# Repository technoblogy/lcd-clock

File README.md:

# Low-Power LCD Clock
A low-power LCD clock based on an AVR128DA48.

For more information see http://www.technoblogy.com/show?19K8.

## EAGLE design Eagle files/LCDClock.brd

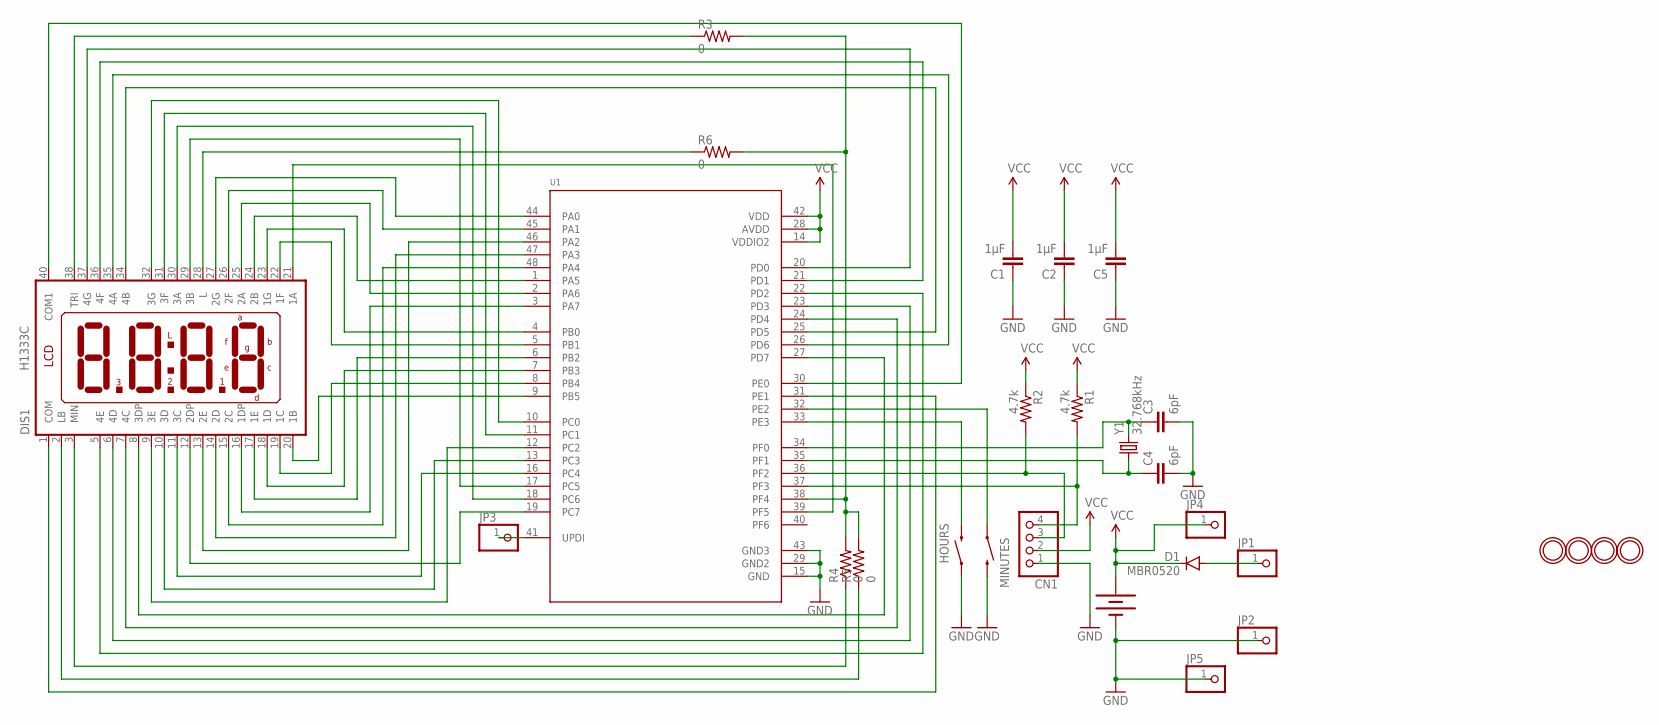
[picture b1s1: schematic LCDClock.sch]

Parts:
BAT1: 20mm coincell; BATTCON_20MM_4LEGS
C1, C2, C5: 1µF; 0805
C3, C4: 6pF; 0805
CN1: JST_4PIN; JSTPH4
D1: MBR0520; SOD-123
DIS1: H1333C
HOURS: SWITCH-MOMENTARY-2SMD-4; TACTILE_SWITCH_TALL
JP1, JP2, JP3: HEADER-1X1ROUND; 1X01_ROUND
JP4, JP5: HEADER-1X12MM; 1X01_2MM
MINUTES: SWITCH-MOMENTARY-2SMD-4; TACTILE_SWITCH_TALL
R1, R2: 4.7k; 0805
R3, R4, R5, R6: 0; 0805
U1: AVR128DB48; LQFP48
U$1, U$4, U$5, U$9: MOUNTINGHOLE2.5; MOUNTINGHOLE_2.5_PLATED
Y1: 32.768kHz; CRYSTAL-SMD-3.2X1.5MM

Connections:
GND: BAT1.NEGATIVE (-), C1.1, C2.1, C3.2, C4.2, C5.1, CN1.1, HOURS.A2 (1), JP2.1, JP5.1, MINUTES.B2 (2), U1.15 (GND), U1.29 (GND2), U1.43 (GND3)
unnamed: DIS1.23 (1G), U1.4 (PB0)
unnamed: DIS1.22 (1F), U1.5 (PB1)
unnamed: DIS1.17 (1E), U1.6 (PB2)
unnamed: DIS1.18 (1D), U1.7 (PB3)
unnamed: DIS1.19 (1C), U1.8 (PB4)
unnamed: DIS1.20 (1B), U1.9 (PB5)
unnamed: DIS1.24 (2B), U1.1 (PA5)
unnamed: DIS1.25 (2A), U1.2 (PA6)
unnamed: DIS1.26 (2F), U1.45 (PA1)
unnamed: MINUTES.A2 (1), U1.32 (PE2)
unnamed: DIS1.27 (2G), U1.44 (PA0)
unnamed: DIS1.16 (1DP), U1.3 (PA7)
unnamed: HOURS.B2 (2), U1.33 (PE3)
unnamed: DIS1.15 (2C), U1.48 (PA4)
unnamed: DIS1.14 (2D), U1.47 (PA3)
unnamed: DIS1.13 (2E), U1.46 (PA2)
unnamed: DIS1.12 (2DP), U1.19 (PC7)
unnamed: DIS1.11 (3C), U1.16 (PC4)
unnamed: DIS1.10 (3D), U1.13 (PC3)
unnamed: DIS1.9 (3E), U1.12 (PC2)
unnamed: DIS1.29 (3B), U1.17 (PC5)
unnamed: DIS1.30 (3A), U1.18 (PC6)
unnamed: DIS1.31 (3F), U1.11 (PC1)
unnamed: DIS1.32 (3G), U1.10 (PC0)
unnamed: DIS1.34 (4B), U1.25 (PD5)
unnamed: DIS1.35 (4A), U1.26 (PD6)
unnamed: CN1.3, R2.2, U1.36 (PF2)
unnamed: DIS1.36 (4F), U1.21 (PD1)
unnamed: CN1.4, R1.2, U1.37 (PF3)
unnamed: DIS1.37 (4G), U1.20 (PD0)
unnamed: DIS1.8 (3DP), U1.27 (PD7)
unnamed: DIS1.7 (4C), U1.24 (PD4)
unnamed: DIS1.6 (4D), U1.23 (PD3)
unnamed: DIS1.5 (4E), U1.22 (PD2)
unnamed: DIS1.21 (1A), U1.39 (PF5)
unnamed: R3.2, R4.2, R5.2, R6.2, U1.38 (PF4)
unnamed: DIS1.40 (COM1), U1.30 (PE0)
unnamed: DIS1.1 (COM), U1.31 (PE1)
unnamed: C4.1, U1.35 (PF1), Y1.P$1 (1)
unnamed: JP3.1, U1.41 (UPDI)
unnamed: C3.1, U1.34 (PF0), Y1.P$2 (2)
unnamed: DIS1.38 (TRI), R3.1
unnamed: DIS1.28 (L), R6.1
unnamed: DIS1.3 (MIN), R4.1
unnamed: DIS1.2 (LB), R5.1
unnamed: D1.A, JP1.1
VCC: BAT1.POSITIVE@1 (+), BAT1.POSITIVE@2 (+), BAT1.POSITIVE@3 (+), BAT1.POSITIVE@4 (+), C1.2, C2.2, C5.2, CN1.2, D1.C, JP4.1, R1.1, R2.1, U1.14 (VDDIO2), U1.28 (AVDD), U1.42 (VDD)

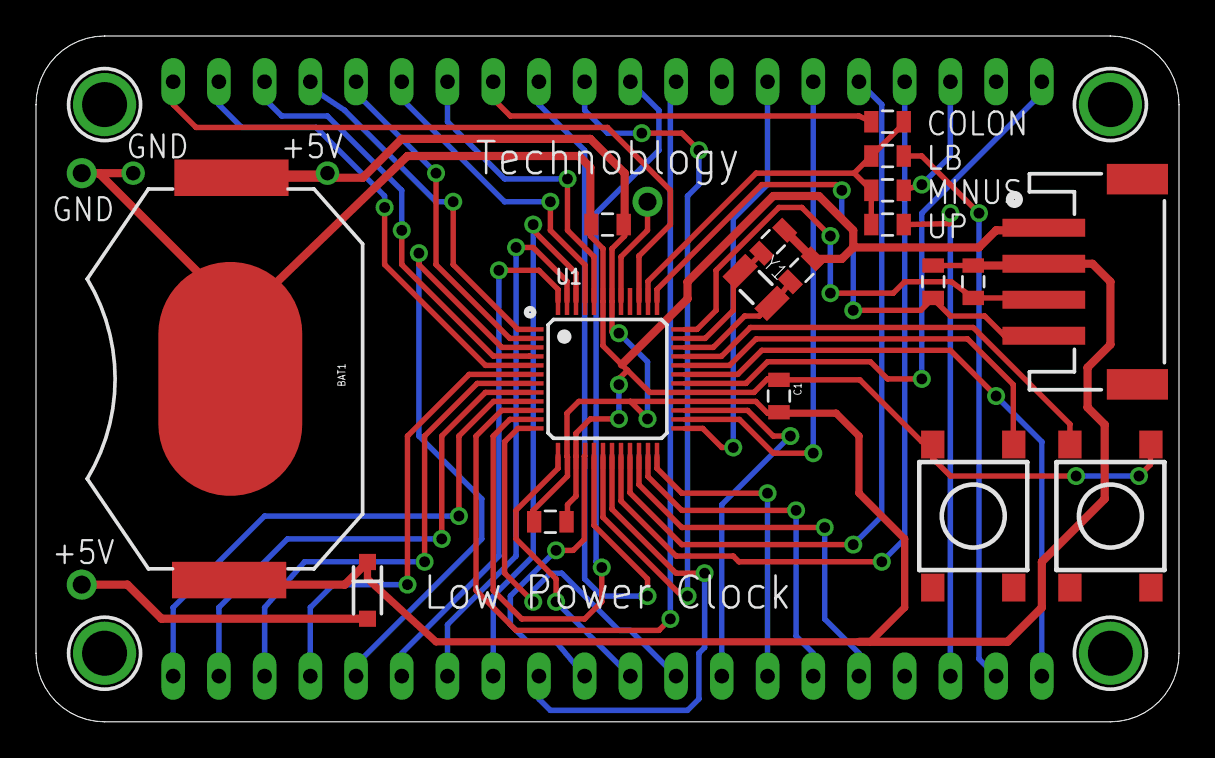
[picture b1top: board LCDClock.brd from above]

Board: 2 copper layers, 63.5 x 38.1 mm, 28 parts (1 on the bottom side), 48 nets.

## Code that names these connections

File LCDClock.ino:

/* Low-Power LCD Clock

   David Johnson-Davies - www.technoblogy.com - 4th May 2021
   AVR128DA48 @ 24 MHz (internal oscillator; BOD disabled)
   
   CC BY 4.0
   Licensed under a Creative Commons Attribution 4.0 International license: 
   http://creativecommons.org/licenses/by/4.0/
*/

#include <avr/io.h>
#include <avr/interrupt.h>
#include <avr/sleep.h>

// Seven segment definitions

const int CharLen = 15;
uint8_t Char[CharLen] = {
//  abcdefg  Segments
  0b1111110, // 0
  0b0110000, // 1
  0b1101101, // 2
  0b1111001, // 3
  0b0110011, // 4
  0b1011011, // 5
  0b1011111, // 6
  0b1110000, // 7
  0b1111111, // 8
  0b1111011, // 9
  0b0000000, // 10  Space
  0b0000001, // 11  '-'
  0b1100011, // 12  Degree
  0b1001110, // 13  'C'
  0b0111110  // 14  'V'
};

const int Space = 10;
const int Minus = 11;
const int Degree = 12;
const int Celsius = 13;
const int Vee = 14;

// Ports **********************************************

PORT_t *Digit[4] = { &PORTD, &PORTC, &PORTA, &PORTB };

void PortSetup () {
  for (int p=0; p<4; p++) Digit[p]->DIR = 0xFF;       // All pins outputs
  PORTE.DIR = PIN0_bm | PIN1_bm;                      // COMs outputs, PE0 and PE1
  PORTF.DIR = PIN5_bm | PIN4_bm;                      // 1A, colon
}

// Real-Time Clock **********************************************

void RTCSetup () {
  uint8_t temp;
  // Initialize 32.768kHz Oscillator:

  // Disable oscillator:
  temp = CLKCTRL.XOSC32KCTRLA & ~CLKCTRL_ENABLE_bm;

  // Enable writing to protected register
  CPU_CCP = CCP_IOREG_gc;
  CLKCTRL.XOSC32KCTRLA = temp;

  while (CLKCTRL.MCLKSTATUS & CLKCTRL_XOSC32KS_bm);   // Wait until XOSC32KS is 0
  
  temp = CLKCTRL.XOSC32KCTRLA | CLKCTRL_LPMODE_bm;      // Use External Crystal & low power
  
  // Enable writing to protected register
  CPU_CCP = CCP_IOREG_gc;
  CLKCTRL.XOSC32KCTRLA = temp;
  
  temp = CLKCTRL.XOSC32KCTRLA | CLKCTRL_ENABLE_bm;    // Enable oscillator
  
  // Enable writing to protected register
  CPU_CCP = CCP_IOREG_gc;
  CLKCTRL.XOSC32KCTRLA = temp;
  
  // Initialize RTC
  while (RTC.STATUS > 0);                             // Wait until registers synchronized

  // 32.768kHz External Crystal Oscillator (XOSC32K)
  RTC.CLKSEL = RTC_CLKSEL_XOSC32K_gc;

  RTC.PITINTCTRL = RTC_PI_bm;                         // Periodic Interrupt: enabled
  
  // RTC Clock Cycles 512, enabled ie 64Hz interrupt
  RTC.PITCTRLA = RTC_PERIOD_CYC512_gc | RTC_PITEN_bm;
}

// ADC Setup **********************************************

void ADCSetup () {
  VREF.ADC0REF = VREF_REFSEL_2V048_gc;
  ADC0.CTRLC = ADC_PRESC_DIV64_gc;                    // 375kHz clock
  VREF.ACREF = VREF_REFSEL_VDD_gc;                    // For voltage measurement
  AC0.DACREF = 64;                                    // DACREF0 voltage VDD*64/256
  ADC0.MUXPOS = ADC_MUXPOS_DACREF0_gc;                // Initially voltage
}

// Display Temperature **********************************************

void DisplayTemp () {
  uint16_t offset = SIGROW.TEMPSENSE1;                // Read offset calibration
  uint16_t slope = SIGROW.TEMPSENSE0;                 // Read slope calibration
  ADC0.MUXPOS = ADC_MUXPOS_TEMPSENSE_gc; 
  ADC0.CTRLA = ADC_ENABLE_bm;                         // Single, 12-bit, left adjust
  ADC0.COMMAND = ADC_STCONV_bm;                       // Start conversion
  while (ADC0.COMMAND & ADC_STCONV_bm);               // Wait for completion
  uint16_t adc_reading = ADC0.RES;                    // ADC conversion result
  uint32_t kelvin = ((uint32_t)(offset - adc_reading) * slope + 0x0800) >> 12;
  int celsius = abs(kelvin - 273);
  ADC0.CTRLA = 0;                                     // Disable ADC

  // Display it
  if (kelvin < 273) Digit[0]->OUT = Char[Minus];
    else Digit[0]->OUT = Char[celsius/10];
  Digit[1]->OUT = Char[celsius%10];
  Digit[2]->OUT = Char[Degree];
  uint8_t units = Char[Celsius];
  Digit[3]->OUT = units;
  PORTF.OUT = (units>>1 & PIN5_bm);                   // No colon
}

// Display Voltage **********************************************

void DisplayVoltage () {
  ADC0.MUXPOS = ADC_MUXPOS_DACREF0_gc;                // Measure DACREF0
  ADC0.CTRLA = ADC_ENABLE_bm;                         // Single, 12-bit, left adjusted
  ADC0.COMMAND = ADC_STCONV_bm;                       // Start conversion
  while (ADC0.COMMAND & ADC_STCONV_bm);               // Wait for completion
  uint16_t adc_reading = ADC0.RES;                    // ADC conversion result
  uint16_t voltage = adc_reading/50;
  ADC0.CTRLA = 0;                                     // Disable ADC

  // Display it
  Digit[0]->OUT = Char[Space];
  Digit[1]->OUT = Char[voltage/10] | 0x80;            // Decimal point
  Digit[2]->OUT = Char[voltage%10];
  uint8_t units = Char[Vee];
  Digit[3]->OUT = units;
  PORTF.OUT = (units>>1 & PIN5_bm);                   // No colon
}

// Display Time **********************************************

void DisplayTime (unsigned long halfsecs) {
  uint8_t minutes = (halfsecs / 120) % 60;
  #ifdef TWELVEHOUR
  uint8_t hours = (halfsecs / 7200) % 12 + 1;
  #else
  uint8_t hours = (halfsecs / 7200) % 24;
  #endif
  Digit[0]->OUT = Char[hours/10];
  Digit[1]->OUT = Char[hours%10];
  Digit[2]->OUT = Char[minutes/10];
  uint8_t units = Char[minutes%10];
  Digit[3]->OUT = units;
  uint8_t colon = (halfsecs & 1)<<4;                  // Toggle colon at 1Hz   
  PORTF.OUT = (units>>1 & PIN5_bm) | colon;
}

// Interrupt Service Routine at 64Hz
ISR(RTC_PIT_vect) {
  static uint8_t cycles = 0;
  static unsigned long halfsecs;
  RTC.PITINTFLAGS = RTC_PI_bm;                        // Clear interrupt flag
  // Toggle segments
  for (int p=0; p<4; p++) Digit[p]->OUTTGL = 0xFF;    // Toggle all PORTA,B,C,D pins
  PORTE.OUTTGL = PIN0_bm | PIN1_bm;                   // Toggle COMs, PE0 and PE1
  PORTF.OUTTGL = PIN5_bm | PIN4_bm;                   // Toggle segment 1A, Colon

  cycles++;
  if (cycles < 32) return;
  cycles = 0;

  // Update time
  halfsecs = (halfsecs+1) % 172800;                   // 24 hours
  uint8_t ticks = halfsecs % 120;                     // Half-second ticks
                 
  if (MinsButton()) halfsecs = ((halfsecs/7200)*60 + (halfsecs/120 + 1)%60)*120;
  if (HoursButton()) halfsecs = halfsecs + 7200;

  if (MinsButton() || HoursButton() || ticks < 108) DisplayTime(halfsecs);
  else if (ticks == 108) DisplayVoltage();
  else if (ticks == 114) DisplayTemp();
}

// Buttons **********************************************

void ButtonSetup () {
  PORTE.PIN3CTRL = PORT_PULLUPEN_bm;                  // PE3 input pullup
  PORTE.PIN2CTRL = PORT_PULLUPEN_bm;                  // PE2 input pullup
}

boolean MinsButton () {
  return (PORTE.IN & PIN2_bm) == 0;                   // True if button pressed
}

boolean HoursButton () {
  return (PORTE.IN & PIN3_bm) == 0;                   // True if button pressed
}

// Sleep **********************************************

void SleepSetup () {
  SLPCTRL.CTRLA |= SLPCTRL_SMODE_PDOWN_gc;
  SLPCTRL.CTRLA |= SLPCTRL_SEN_bm;
}

// Setup **********************************************

void setup () {
  PortSetup();
  ButtonSetup();
  SleepSetup();
  RTCSetup();
  ADCSetup();
}

// Just stay asleep to save power unless woken by an interrupt
void loop () {
  sleep_cpu();
}

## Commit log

2021-05-04 Version 1 - 4th May 2021

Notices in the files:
parts and their libraries:
SparkFun-Electromechanical: Licensing: Creative Commons ShareAlike 4.0 International - https://creativecommons.org/licenses/by-sa/4.0
microbuilder: This work is placed in the public domain, and may be freely used for commercial and non-commercial work with the following conditions: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
